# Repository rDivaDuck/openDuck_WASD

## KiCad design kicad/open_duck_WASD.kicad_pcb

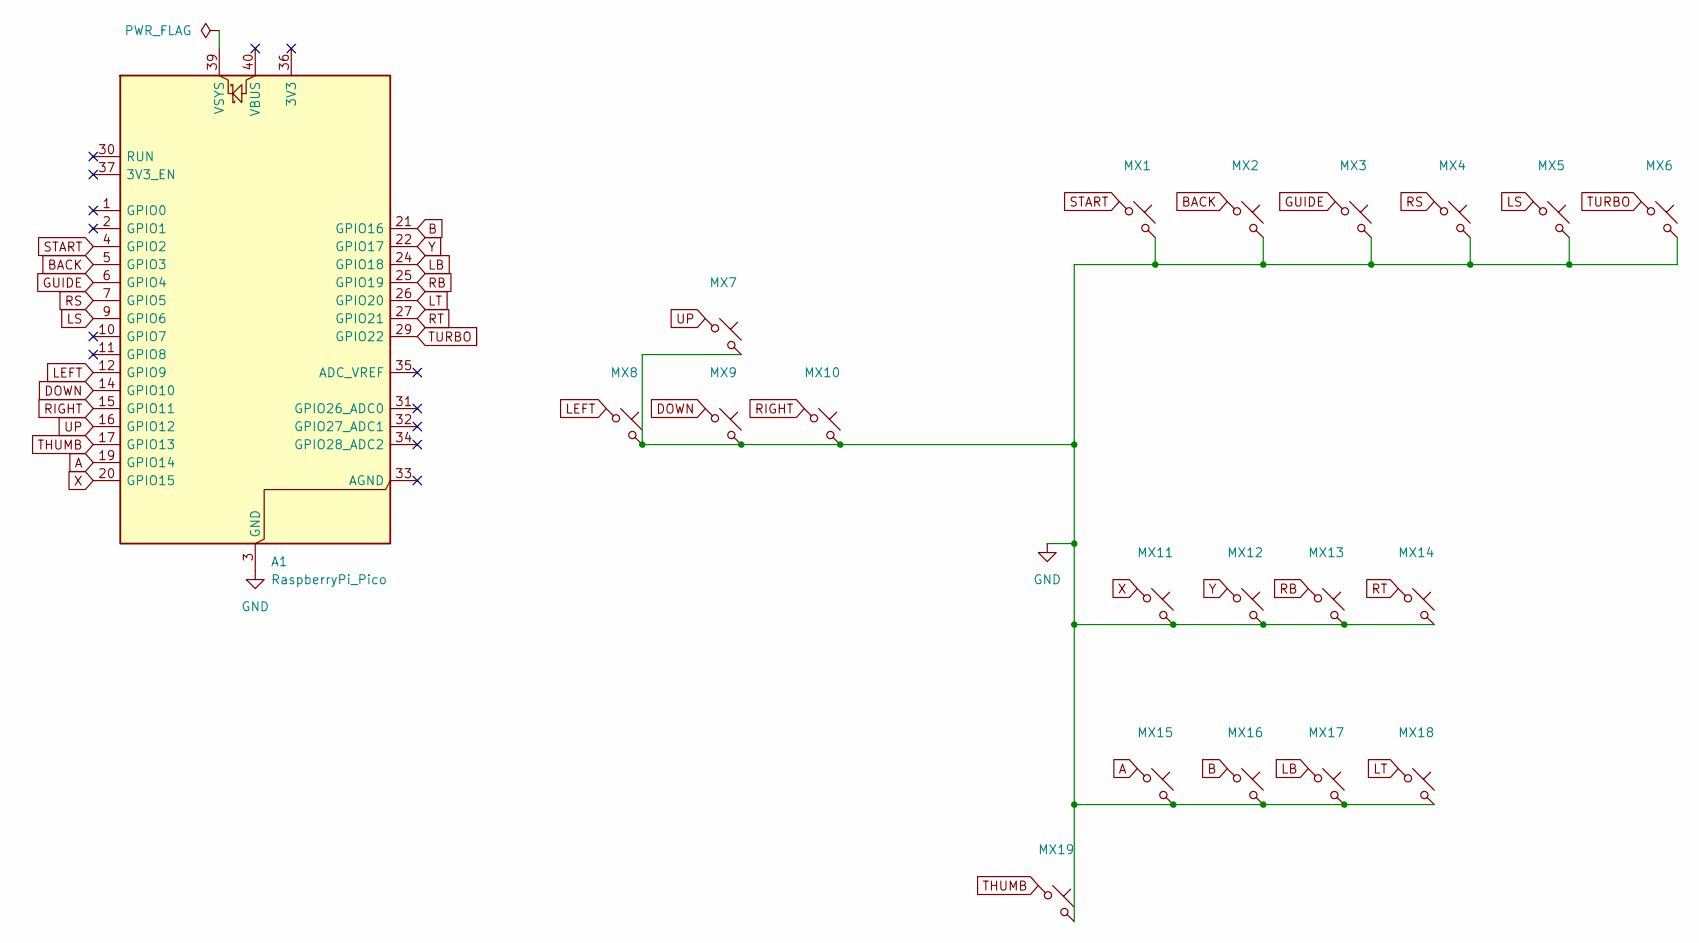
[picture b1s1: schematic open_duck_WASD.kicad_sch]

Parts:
A1: RaspberryPi_Pico; RaspberryPi_Pico_Common_Unspecified
MX1, MX2, MX3, MX4, MX5, MX6, MX7, MX8, MX9, MX10, MX11, MX12, MX13, MX14, MX15, MX16, MX17, MX18, MX19: SW_Push_45deg; MX-Hotswap-1U; LCSC C2803348

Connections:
A: A1.19 (GPIO14), MX15.1
B: A1.21 (GPIO16), MX16.1
BACK: A1.5 (GPIO3), MX2.1
DOWN: A1.14 (GPIO10), MX9.1
GND: A1.3 (GND), A1.8 (GND), A1.13 (GND), A1.18 (GND), A1.23 (GND), A1.28 (GND), A1.38 (GND), MX1.2, MX2.2, MX3.2, MX4.2, MX5.2, MX6.2, MX7.2, MX8.2, MX9.2, MX10.2, MX11.2, MX12.2, MX13.2, MX14.2, MX15.2, MX16.2, MX17.2, MX18.2, MX19.2
GUIDE: A1.6 (GPIO4), MX3.1
LB: A1.24 (GPIO18), MX17.1
LEFT: A1.12 (GPIO9), MX8.1
LS: A1.9 (GPIO6), MX5.1
LT: A1.26 (GPIO20), MX18.1
RB: A1.25 (GPIO19), MX13.1
RIGHT: A1.15 (GPIO11), MX10.1
RS: A1.7 (GPIO5), MX4.1
RT: A1.27 (GPIO21), MX14.1
START: A1.4 (GPIO2), MX1.1
THUMB: A1.17 (GPIO13), MX19.1
TURBO: A1.29 (GPIO22), MX6.1
UP: A1.16 (GPIO12), MX7.1
X: A1.20 (GPIO15), MX11.1
Y: A1.22 (GPIO17), MX12.1

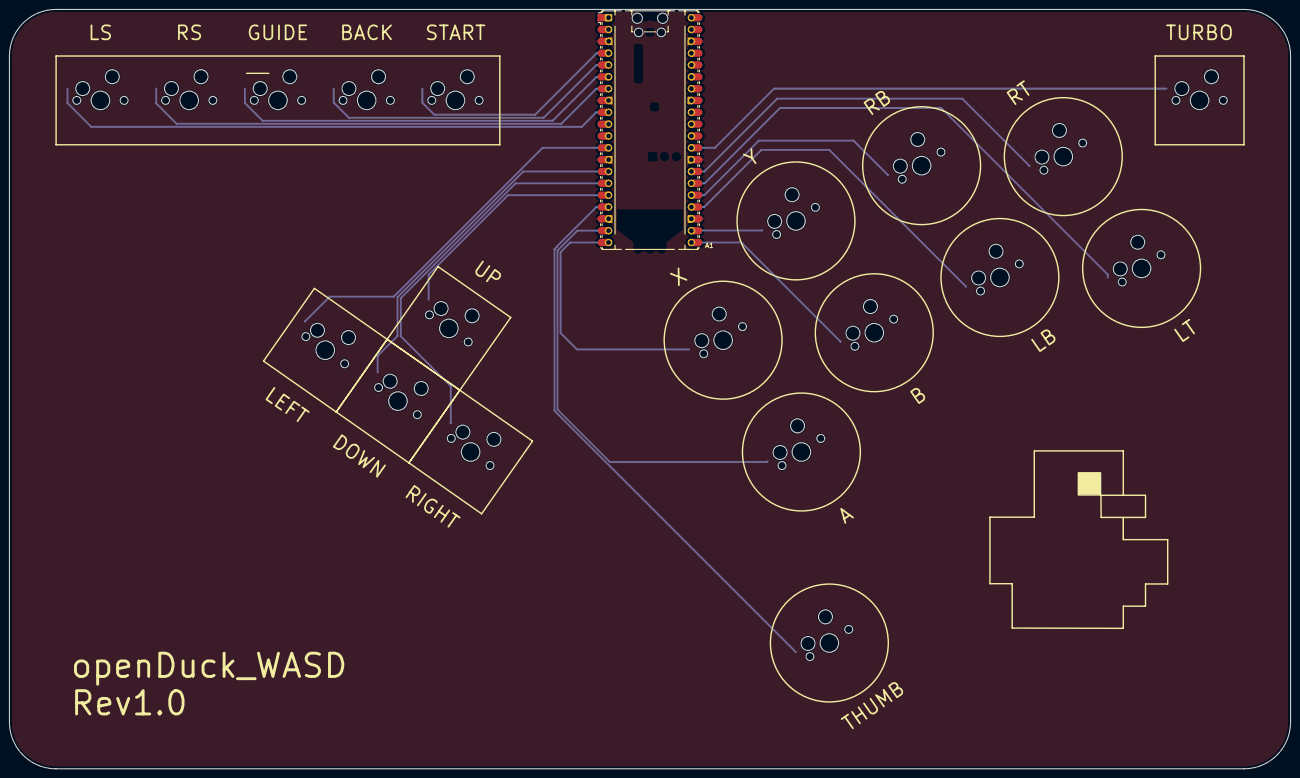
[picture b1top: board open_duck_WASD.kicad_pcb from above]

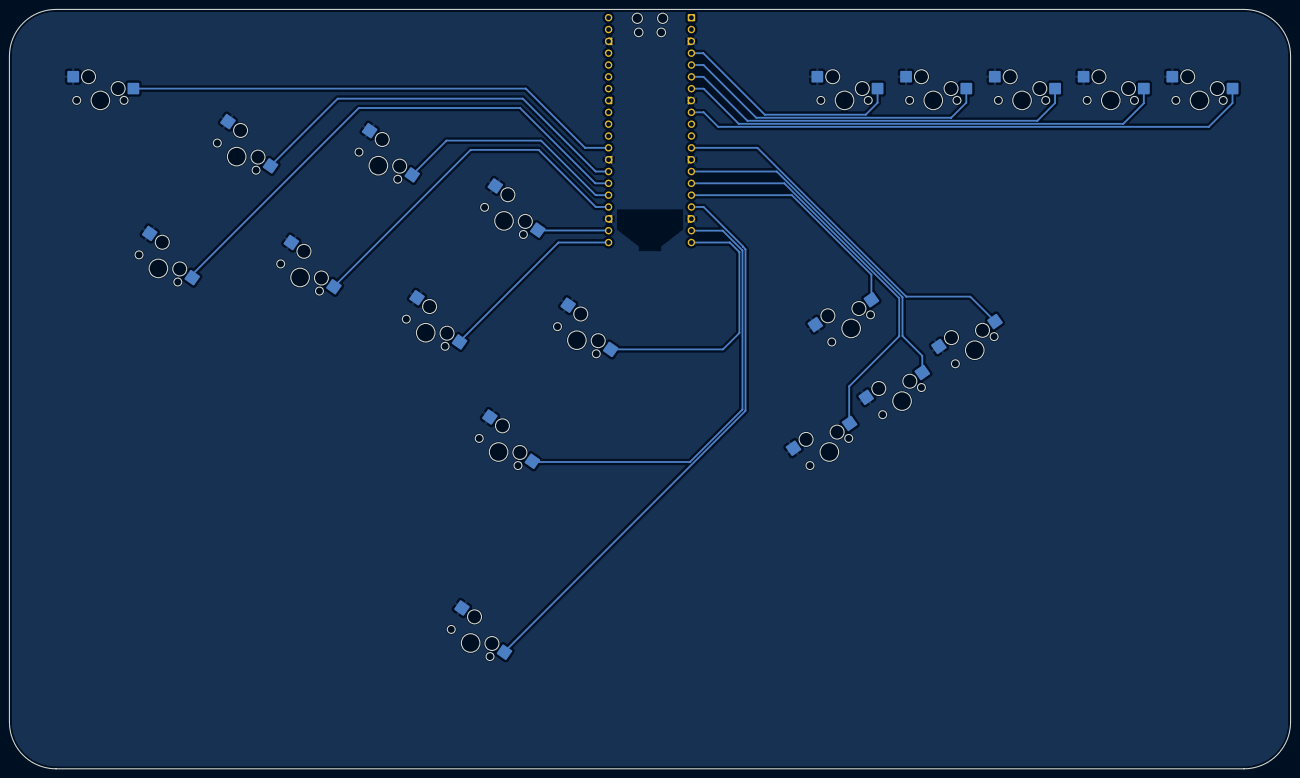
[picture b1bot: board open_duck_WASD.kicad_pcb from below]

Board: 2 copper layers, 275.0 x 163.0 mm, 20 parts (19 on the bottom side), 20 nets.

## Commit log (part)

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2026-03-11 footprint update
2026-03-11 layout
2026-03-11 spelling
2026-03-11 Update label on turbo
2026-03-18 fix 3d model
2026-03-18 Fix LCSC
2026-03-22 fix spelling
